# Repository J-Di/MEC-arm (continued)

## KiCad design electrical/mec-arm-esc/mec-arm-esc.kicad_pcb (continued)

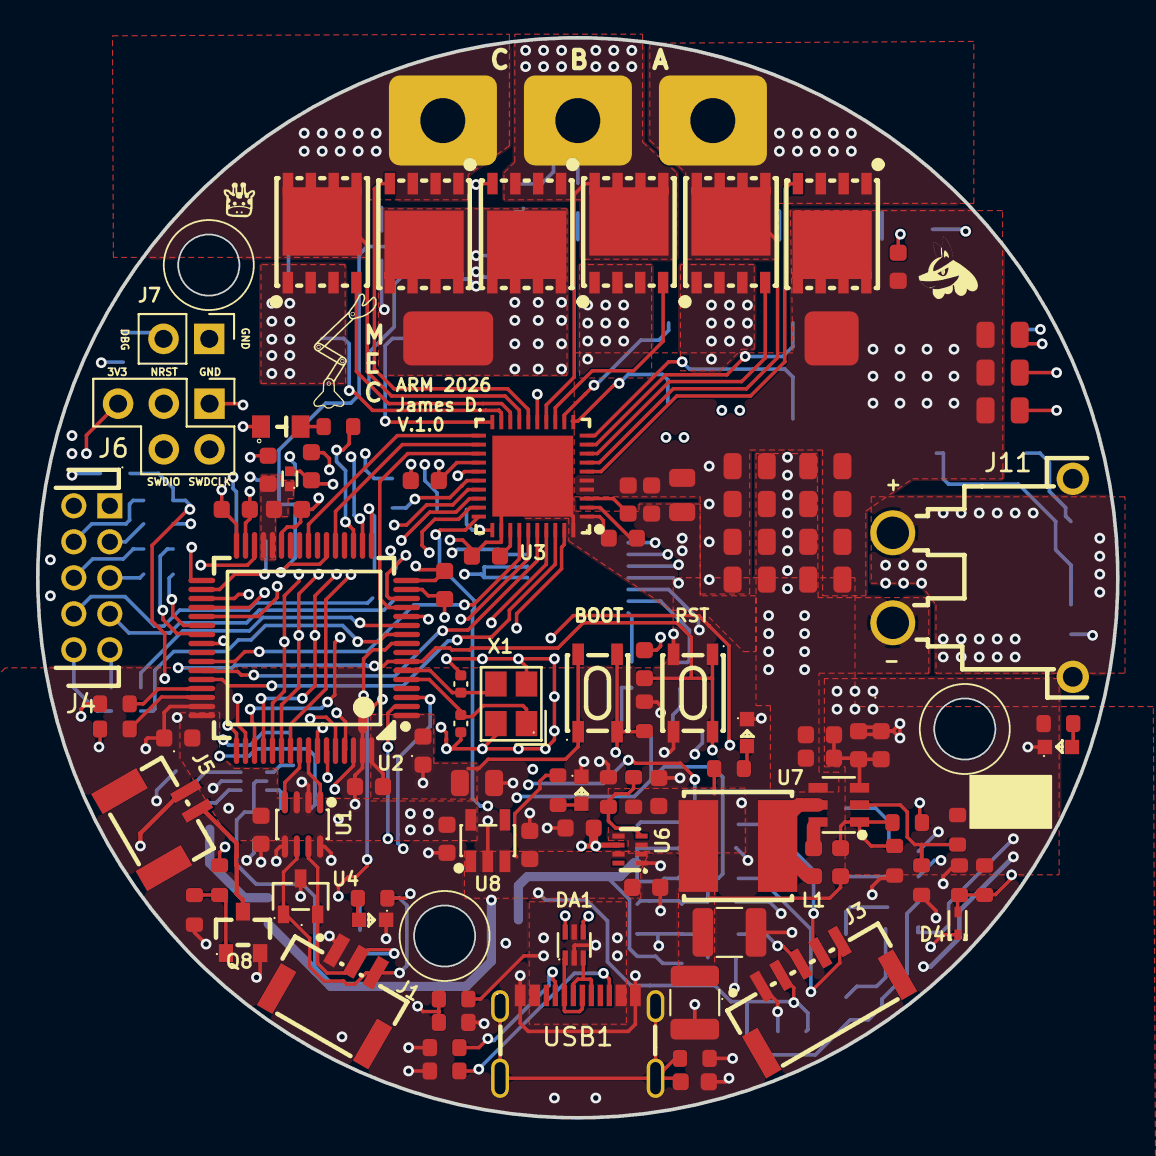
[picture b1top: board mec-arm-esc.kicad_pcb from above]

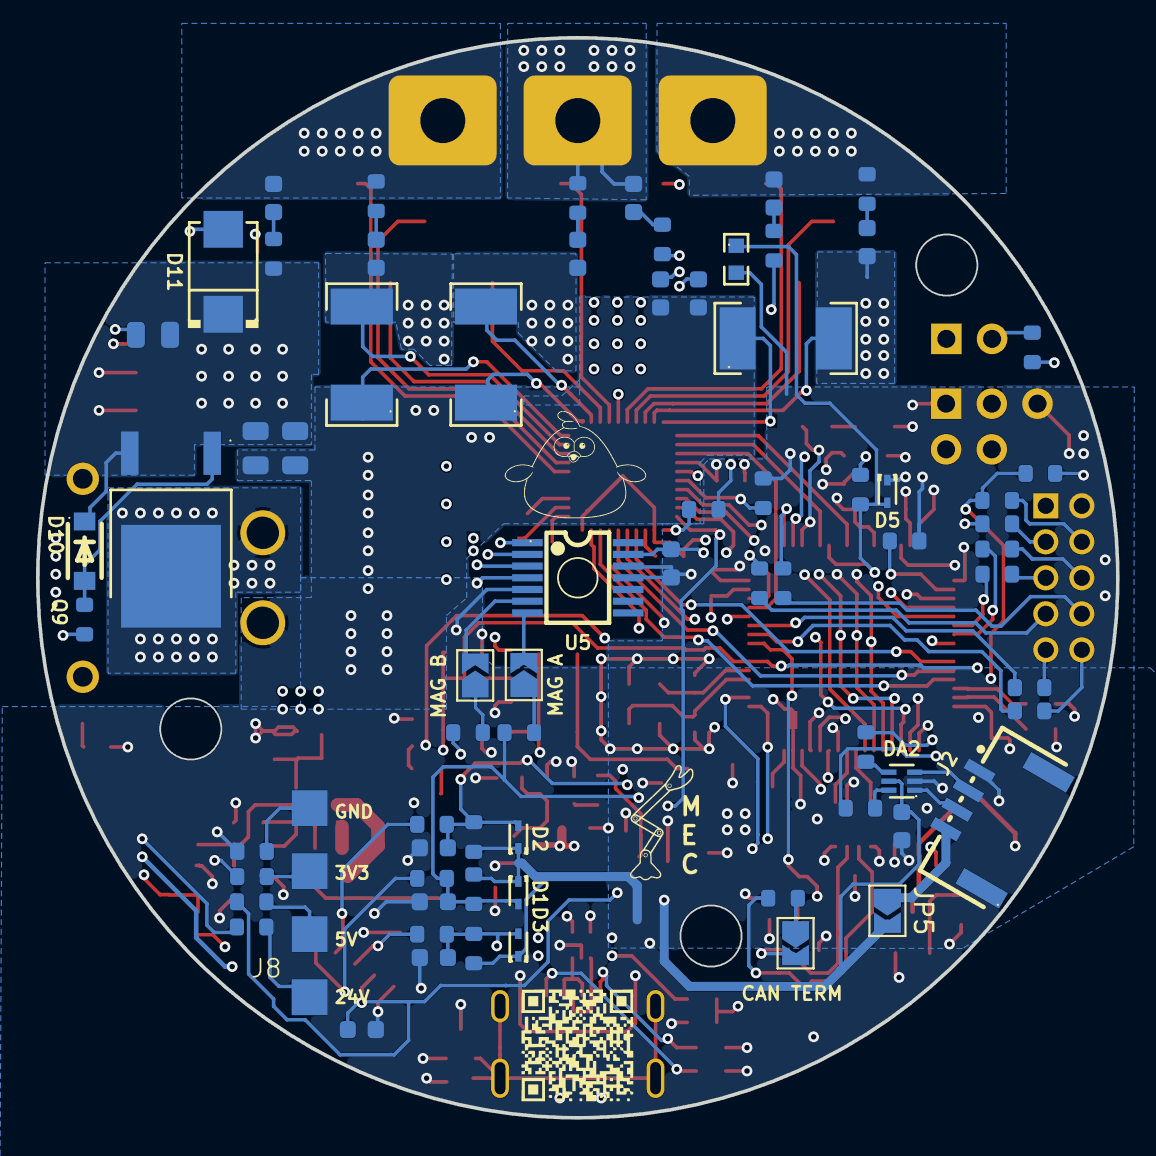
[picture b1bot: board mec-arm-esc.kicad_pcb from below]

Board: 4 copper layers, 60.0 x 60.0 mm, 178 parts (72 on the bottom side), 125 nets.

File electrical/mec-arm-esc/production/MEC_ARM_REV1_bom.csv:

Designator,Footprint,Quantity,Value,LCSC Part #
"C10, C11, C16, C44, C45, C7, C8, C9",C_0603,8,100nf,C108079
C12,C_0805,1,10uf,C711098
"C13, C43",C_0603,2,10nf,C519406
"C14, C15, C49, C58, C59, C60, C61",C_0603,7,1uf,C106248
"C17, C18",0402,2,16pF,C5142569
C19,C_0603,1,1uF,C14664
C20,C_0603,1,47nF,C513577
C21,C_0603,1,0.1uF,C14663
"C22, C28, C29",C_0805,3,10uF,C162422
C23,C_0603,1,1uF 6.3V,C2169508
"C24, C42, C62",C_0603,3,0.1uF,C108079
"C25, C26, C27, C50, C53, C54",C_0603,6,1uF,C559769
"C30, C31, C32, C33, C34, C35, C36, C37, C38, C39, C40, C41",C_0805,12,15uF,C162422
"C46, C47, C48",C_0603,3,10pF,C2168592
"C51, C52",C_0603,2,100nF,C14663
"C55, C56",1210,2,47uF,C77101
C57,C_0603,1,1pF,C29936
"D1, D2, D3, D4, D5",SOD-523_L1.2-W0.8-LS1.6-RD-1,5,BAT30KFILM,C2926449
D10,SOD-123F_L2.8-W1.8-LS3.7-RD,1,12V,C177013
D11,SMB_L4.6-W3.6-LS5.3-RD,1,SMBJ30A-TR,C133663
"DA1, DA2",SOT-666-6_L1.6-W1.2-P0.50-LS1.6-BR,2,USBLC6-2P6,C15999
FB1,L0402,1,BLM15BX601SN1D,C710336
J1,CONN-SMD_GT-A1257WRS-103SBT01,1,GT-A1257WRS-103SBT01,C22472755
J10,PHASE_PAD,1,~,
J11,CONN-TH_XT30PW-M,1,XT30PW-M,C431092
J12,3x3BusBar Pad,1,~,
J3,CONN-SMD_5P-P1.25_SM05B-GHS-TB-LF-SN,1,SM05B-GHS-TB,C189896
J5,CONN-SMD_SM02B-GHS-TB-LF-SN,1,XY-SM02B-GHS-TB,C54582897
J8,TestPadArray1x4,1,~,
J9,5x3BusBar Pad,1,~,
L1,IND-SMD_L6.0-W6.0_VLS6045EX,1,15uH,C404502
"LED1, LED2, LED3, LED6",LED0603-RD_RED,4,150060RS75000,C3030991
LED5,LED0805-RD,1,LTST-C171KGKT,C98224
"Q1, Q2, Q3, Q4, Q5, Q6",DFN-8_L5.8-W4.9-P1.27-LS6.0-BL-1,6,STL110N10F7,C672185
Q8,SOT-23_L2.9-W1.3-P1.90-LS2.4-BR,1,PJA138K_R1_00001,C2902548
Q9,TO-252-2_L6.6-W6.1-P4.58-LS9.9-TL,1,TJ60S04M3L-VB,C7494452
"R1, R2, R3",RES-SMD_L6.3-W3.2_R2512,3,PEWF2512D2L00Q9,C19697176
"R11, R15, R24, R59",R_0603,4,10k,C98220
"R12, R23",R_0603,2,2.55M,C54102347
R13,R_0603,1,200k,C2907009
R14,R_0603,1,0,C2906974
"R16, R17",R_0603,2,10,C844919
"R18, R19, R54",R_0603,3,5.1k,C2907044
"R20, R21, R33, R44",R_0603,4,100k,C2906980
R22,R_0603,1,120,C2906988
"R27, R28, R29, R30, R31, R32, R70, R71",R_0603,8,1.8k,C286575
R34,R_0603,1,6.34k,C321969
R35,R_0603,1,3.24k,C728589
"R36, R37, R38, R39, R40, R41, R46, R47, R48, R50, R51, R52, R53, R55, R56, R57, R58, R60, R61, R68, R69",R_0603,21,1k,C14676
R4,R0603,1,10k,C153011
R42,R_0603,1,100k 0.5%,C122538
R43,R_0603,1,19.1k 0.5%,C861184
R45,R_0603,1,40.2k,C286588
R49,R_0603,1,500,C73811
"SW1, SW2",SW-SMD_4P-L4.2-W3.4-P2.15-LS5.2,2,SH-1808SN-250GF,C52092028
U1,SOT-23-8_L2.9-W1.6-P0.65-LS2.8-BR,1,TCAN330DCNT,C2671056
U2,LQFP-64_L10.0-W10.0-P0.50-LS12.0-BL,1,STM32G474RET3,C1236669
U3,WQFN-40_L6.0-W6.0-P0.50-TL-EP4.5,1,DRV8323SRTAT,C2150452
U4,SOT-23-3_L2.9-W1.3-P1.90-LS2.4-BR,1,ESD2CAN24DBZRQ1,C5736151
U5,TSSOP-14_L5.0-W4.4-P0.65-LS6.4-BL,1,AS5047P-ATSM_C22459881,C22459881
U6,SOT-583-8_L2.1-W1.6-P0.50-LS1.6-BL,1,TPS2116DRLR,C3235557
U7,SOT-23-6_L2.9-W1.6-P0.95-LS2.9-BL,1,LMR51625XDDCR_C44750835,C44750835
U8,SOT-23-5_L3.0-W1.6-P0.95-LS2.8-BR,1,AP7366EA-33W5-7,C22038443
USB1,USB-C-SMD_GT-USB-7010B,1,USB4215-03-A,C37616412
X1,CRYSTAL-SMD_4P-L3.2-W2.5-BL,1,3225 8M 12PF 10PPM,C5181478

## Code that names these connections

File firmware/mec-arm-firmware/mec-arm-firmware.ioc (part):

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Mcu.Name=STM32G474R(B-C-E)Tx
Mcu.Package=LQFP64
Mcu.UserName=STM32G474RETx
PA0.Mode=IN1-Single-Ended
PA0.Signal=ADC2_IN1
PA1.Signal=SharedAnalog_PA1
PA10.Signal=S_TIM1_CH3
PA11.Mode=Device
PA11.Signal=USB_DM
PA12.Mode=Device
PA12.Signal=USB_DP
PA13.Mode=Serial_Wire
PA13.Signal=SYS_JTMS-SWDIO
PA14.Mode=Serial_Wire
PA14.Signal=SYS_JTCK-SWCLK
PA15.GPIOParameters=GPIO_Speed,PinState,GPIO_Label
PA15.GPIO_Label=ENC_CS
PA15.GPIO_Speed=GPIO_SPEED_FREQ_HIGH
PA15.PinState=GPIO_PIN_SET
PA15.Signal=GPIO_Output
PA2.Mode=IN3-Single-Ended
PA2.Signal=ADC1_IN3
PA3.Mode=IN4-Single-Ended
PA3.Signal=ADC1_IN4
PA4.Signal=COMP_DAC11_group
PA5.GPIOParameters=GPIO_Label
PA5.GPIO_Label=LED_DEBUG1
PA5.Signal=GPIO_Output
PA7.Signal=SharedAnalog_PA7
PA8.Signal=S_TIM1_CH1
PA9.Signal=S_TIM1_CH2
PB0.Signal=SharedAnalog_PB0
PB10.Mode=Asynchronous
PB10.Signal=USART3_TX
PB11.Mode=Asynchronous
PB11.Signal=USART3_RX
PB12.Mode=Activate-Break-Input
PB12.Signal=TIM1_BKIN
PB13.Mode=PWM Generation1 CH1 CH1N
PB13.Signal=TIM1_CH1N
PB14.Mode=PWM Generation2 CH2 CH2N
PB14.Signal=TIM1_CH2N
PB15.Mode=PWM Generation3 CH3 CH3N
PB15.Signal=TIM1_CH3N
PB3.Mode=FDCAN_Activate
PB3.Signal=FDCAN3_RX
PB4.Mode=FDCAN_Activate
PB4.Signal=FDCAN3_TX
PB5.GPIOParameters=GPIO_Label
PB5.GPIO_Label=ENC_Z
PB5.Signal=GPXTI5
PB6.Signal=S_TIM4_CH1
PB7.Signal=S_TIM4_CH2
PB9.GPIOParameters=GPIO_Label
PB9.GPIO_Label=DRV_ENABLE
PB9.Signal=GPIO_Output
PC1.GPIOParameters=GPIO_Label
PC1.GPIO_Label=USB_VBUS_SENSE
PC1.Signal=GPXTI1
PC10.Mode=Full_Duplex_Master
PC10.Signal=SPI3_SCK
PC11.Mode=Full_Duplex_Master
PC11.Signal=SPI3_MISO
PC12.Mode=Full_Duplex_Master
PC12.Signal=SPI3_MOSI
PC13.GPIOParameters=GPIO_Label
PC13.GPIO_Label=LAZER_EN
PC13.Signal=GPIO_Output
PC14-OSC32_IN.GPIOParameters=GPIO_Label
PC14-OSC32_IN.GPIO_Label=FAN_EN
PC14-OSC32_IN.Signal=GPIO_Output
PC2.Mode=IN8-Single-Ended
PC2.Signal=ADC1_IN8
PC3.Mode=IN9-Single-Ended
PC3.Signal=ADC1_IN9
PC4.Mode=IN5-Single-Ended
PC4.Signal=ADC2_IN5
PC6.GPIOParameters=GPIO_Label
PC6.GPIO_Label=GPIO_SPARE1
PC6.Signal=GPIO_Output
PC7.GPIOParameters=GPIO_Label
PC7.GPIO_Label=GPIO_SPARE2
PC7.Signal=GPIO_Output
PC8.GPIOParameters=GPIO_Label
PC8.GPIO_Label=GPIO_SPARE3
PC8.Signal=GPIO_Output
PD2.GPIOParameters=GPIO_Speed,PinState,GPIO_Label
PD2.GPIO_Label=DRV_nSCS
PD2.GPIO_Speed=GPIO_SPEED_FREQ_HIGH
PD2.PinState=GPIO_PIN_SET
PD2.Signal=GPIO_Output
PF0-OSC_IN.Mode=HSE-External-Oscillator
PF0-OSC_IN.Signal=RCC_OSC_IN
PF1-OSC_OUT.Mode=HSE-External-Oscillator
PF1-OSC_OUT.Signal=RCC_OSC_OUT
RCC.HSE_VALUE=8000000
RCC.SYSCLKFreq_VALUE=170000000
RCC.SYSCLKSource=RCC_SYSCLKSOURCE_PLLCLK
board=custom

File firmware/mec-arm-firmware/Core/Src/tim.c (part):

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
    __HAL_RCC_GPIOB_CLK_ENABLE();
    /**TIM1 GPIO Configuration
    PB12     ------> TIM1_BKIN
    */
    GPIO_InitStruct.Pin = GPIO_PIN_12;
    GPIO_InitStruct.Mode = GPIO_MODE_AF_OD;
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
    __HAL_RCC_GPIOB_CLK_ENABLE();
    /**TIM4 GPIO Configuration
    PB6     ------> TIM4_CH1
    PB7     ------> TIM4_CH2
    */
    GPIO_InitStruct.Pin = GPIO_PIN_6|GPIO_PIN_7;
    GPIO_InitStruct.Mode = GPIO_MODE_AF_PP;
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    __HAL_RCC_GPIOB_CLK_ENABLE();
    __HAL_RCC_GPIOA_CLK_ENABLE();
    /**TIM1 GPIO Configuration
    PB13     ------> TIM1_CH1N
    PB14     ------> TIM1_CH2N
    PB15     ------> TIM1_CH3N
    PA8     ------> TIM1_CH1
    PA9     ------> TIM1_CH2
    PA10     ------> TIM1_CH3
    */
    GPIO_InitStruct.Pin = GPIO_PIN_13|GPIO_PIN_14;
    GPIO_InitStruct.Mode = GPIO_MODE_AF_PP;
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    __HAL_RCC_TIM1_CLK_DISABLE();

    /**TIM1 GPIO Configuration
    PB12     ------> TIM1_BKIN
    PB13     ------> TIM1_CH1N
    PB14     ------> TIM1_CH2N
    PB15     ------> TIM1_CH3N
    PA8     ------> TIM1_CH1
    PA9     ------> TIM1_CH2
    PA10     ------> TIM1_CH3
    */
    HAL_GPIO_DeInit(GPIOB, GPIO_PIN_12|GPIO_PIN_13|GPIO_PIN_14|GPIO_PIN_15);

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    __HAL_RCC_TIM4_CLK_DISABLE();

    /**TIM4 GPIO Configuration
    PB6     ------> TIM4_CH1
    PB7     ------> TIM4_CH2
    */
    HAL_GPIO_DeInit(GPIOB, GPIO_PIN_6|GPIO_PIN_7);

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
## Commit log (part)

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2026-06-17 Added project folders
2026-06-23 initial project creation
2026-06-23 first half bridge added
2026-06-23 fixed mosfet symbol
2026-06-24 finish single phase
2026-06-25 added mcu sheet
2026-06-25 shunt phase a added
2026-06-26 added MCU power and ground + altered symbol
